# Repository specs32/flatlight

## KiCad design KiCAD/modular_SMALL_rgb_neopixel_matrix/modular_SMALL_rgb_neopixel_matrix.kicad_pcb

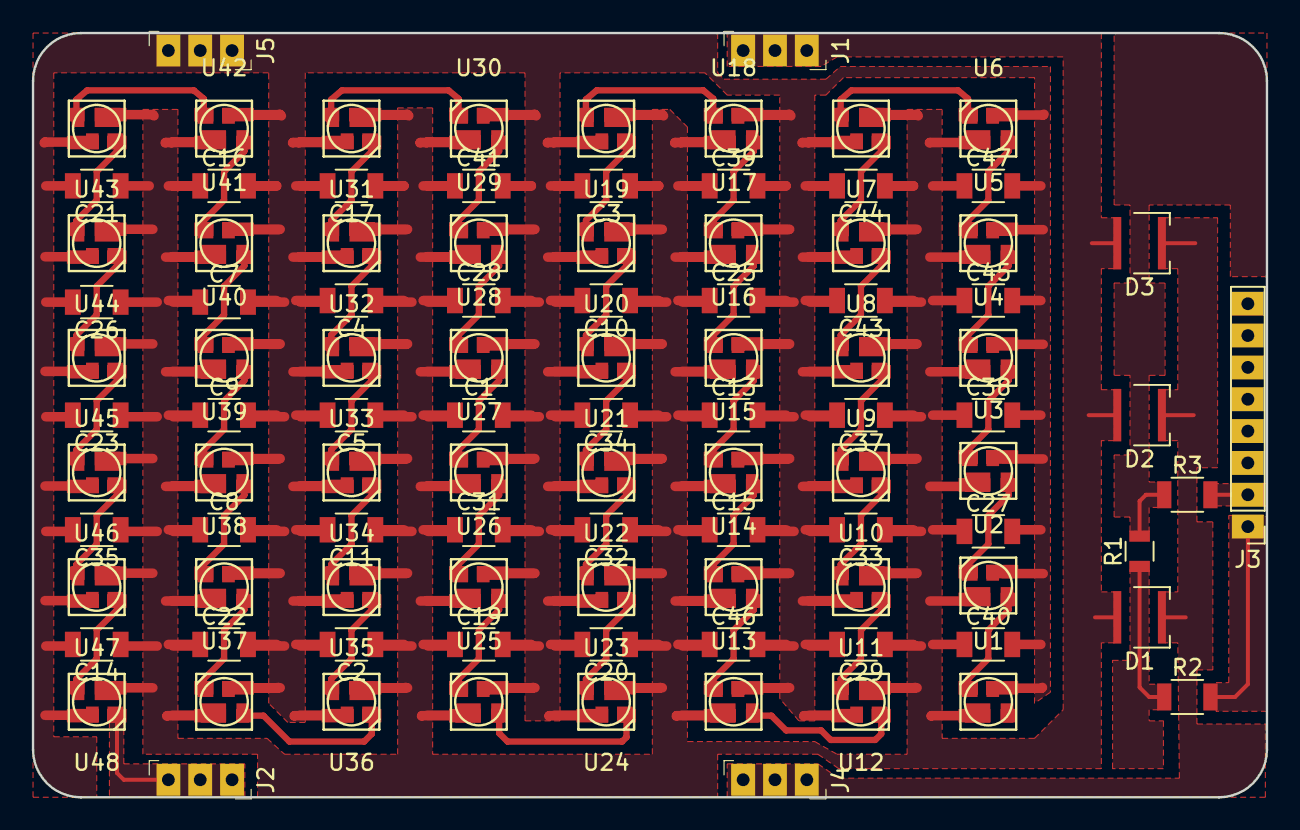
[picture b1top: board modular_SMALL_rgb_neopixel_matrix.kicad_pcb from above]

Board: 2 copper layers, 77.5 x 48.0 mm, 99 parts (0 on the bottom side), 55 nets.

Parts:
C1, C2, C3, C4, C5, C7, C8, C9, C10, C11, C13, C14, C15, C16, C17, C19, C20, C21, C22, C23, C25, C26, C27, C28, C29, C31, C32, C33, C34, C35, C37, C38, C39, C40, C41, C43, C44, C45, C46, C47: 100nF; C_1206
D1, D2, D3: CREE_XP; LED_Cree-XP_x
J1, J2, J4, J5: CONN_01X03; 3pin_through_conn
J3: CONN_01X08; 1x08_Pitch2.00mm_Bigpad
R1: 15KΩ_NTC; R_0805
R2, R3: 0Ω_Bridge; R_1206
U1, U2, U3, U4, U5, U6, U7, U8, U9, U10, U11, U12, U13, U14, U15, U16, U17, U18, U19, U20, U21, U22, U23, U24, U25, U26, U27, U28, U29, U30, U31, U32, U33, U34, U35, U36, U37, U38, U39, U40, U41, U42, U43, U44, U45, U46, U47, U48: RGB_ws2812_3535; SK6812_MINI_right

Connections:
GND: C1.2, C2.2, C3.2, C4.2, C5.2, C7.2, C8.2, C9.2, C10.2, C11.2, C13.2, C14.2, C15.2, C16.2, C17.2, C19.2, C20.2, C21.2, C22.2, C23.2, C25.2, C26.2, C27.2, C28.2, C29.2, C31.2, C32.2, C33.2, C34.2, C35.2, C37.2, C38.2, C39.2, C40.2, C41.2, C43.2, C44.2, C45.2, C46.2, C47.2, J5.1, J5.2, J5.3, U1.2, U2.2, U3.2, U4.2, U5.2, U6.2, U7.2, U8.2, U9.2, U10.2, U11.2, U12.2, U13.2, U14.2, U15.2, U16.2, U17.2, U18.2, U19.2, U20.2, U21.2, U22.2, U23.2, U24.2, U25.2, U26.2, U27.2, U28.2, U29.2, U30.2, U31.2, U32.2, U33.2, U34.2, U35.2, U36.2, U37.2, U38.2, U39.2, U40.2, U41.2, U42.2, U43.2, U44.2, U45.2, U46.2, U47.2, U48.2
unnamed: J3.1, R2.2
unnamed: J3.2, R3.2
unnamed: R1.1, R2.1
unnamed: R1.2, R3.1
unnamed: U1.3, U2.1
unnamed: U2.3, U3.1
unnamed: U3.3, U4.1
unnamed: U4.3, U5.1
unnamed: U5.3, U6.1
unnamed: U6.3, U7.1
unnamed: U7.3, U8.1
unnamed: U8.3, U9.1
unnamed: U9.3, U10.1
unnamed: U10.3, U11.1
unnamed: U11.3, U12.1
unnamed: U12.3, U13.1
unnamed: U13.3, U14.1
unnamed: U14.3, U15.1
unnamed: U15.3, U16.1
unnamed: U16.3, U17.1
unnamed: U17.3, U18.1
unnamed: U18.3, U19.1
unnamed: U19.3, U20.1
unnamed: U20.3, U21.1
unnamed: U21.3, U22.1
unnamed: U22.3, U23.1
unnamed: U23.3, U24.1
unnamed: U24.3, U25.1
unnamed: U25.3, U26.1
unnamed: U26.3, U27.1
unnamed: U27.3, U28.1
unnamed: U28.3, U29.1
unnamed: U29.3, U30.1
unnamed: U30.3, U31.1
unnamed: U31.3, U32.1
unnamed: U32.3, U33.1
unnamed: U33.3, U34.1
unnamed: U34.3, U35.1
unnamed: U35.3, U36.1
unnamed: U36.3, U37.1
unnamed: U37.3, U38.1
unnamed: U38.3, U39.1
unnamed: U39.3, U40.1
unnamed: U40.3, U41.1
unnamed: U41.3, U42.1
unnamed: U42.3, U43.1
unnamed: U43.3, U44.1
unnamed: U44.3, U45.1
unnamed: U45.3, U46.1
unnamed: U46.3, U47.1
unnamed: U47.3, U48.1
OCA_1: J2.1, J2.2, J2.3, U48.3
PWM_1: D1.1, D2.1, D3.1, J4.1, J4.2, J4.3
VCC: C1.1, C2.1, C3.1, C4.1, C5.1, C7.1, C8.1, C9.1, C10.1, C11.1, C13.1, C14.1, C15.1, C16.1, C17.1, C19.1, C20.1, C21.1, C22.1, C23.1, C25.1, C26.1, C27.1, C28.1, C29.1, C31.1, C32.1, C33.1, C34.1, C35.1, C37.1, C38.1, C39.1, C40.1, C41.1, C43.1, C44.1, C45.1, C46.1, C47.1, D1.2, D2.2, D3.2, J1.1, J1.2, J1.3, U1.4, U2.4, U3.4, U4.4, U5.4, U6.4, U7.4, U8.4, U9.4, U10.4, U11.4, U12.4, U13.4, U14.4, U15.4, U16.4, U17.4, U18.4, U19.4, U20.4, U21.4, U22.4, U23.4, U24.4, U25.4, U26.4, U27.4, U28.4, U29.4, U30.4, U31.4, U32.4, U33.4, U34.4, U35.4, U36.4, U37.4, U38.4, U39.4, U40.4, U41.4, U42.4, U43.4, U44.4, U45.4, U46.4, U47.4, U48.4

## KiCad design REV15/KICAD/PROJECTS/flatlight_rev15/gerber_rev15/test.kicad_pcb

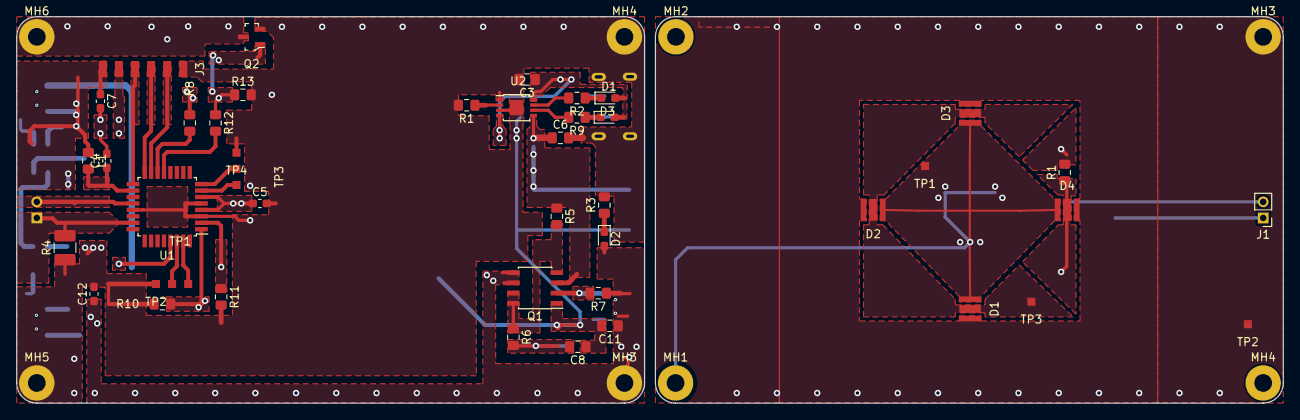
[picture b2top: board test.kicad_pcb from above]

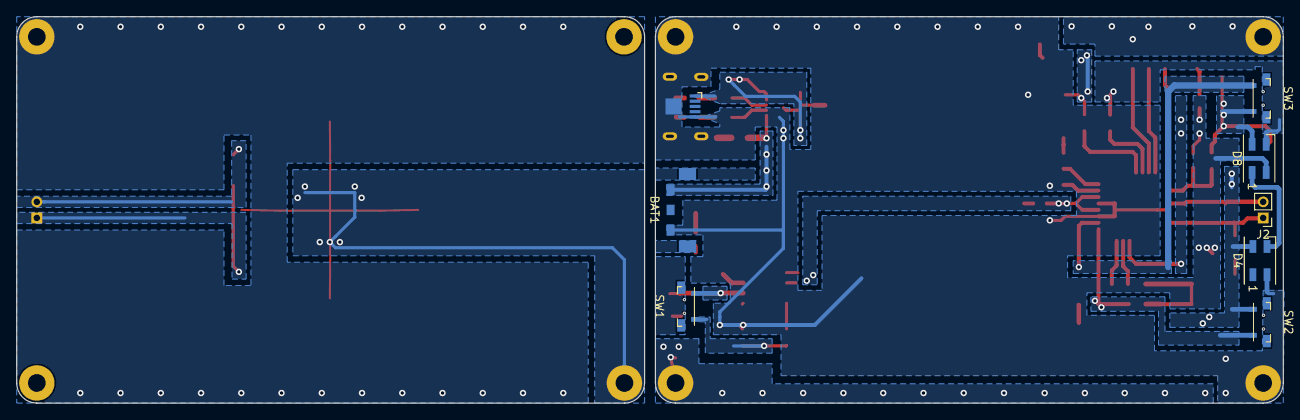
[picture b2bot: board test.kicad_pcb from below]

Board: 2 copper layers, 157.3 x 48.0 mm, 59 parts (8 on the bottom side), 35 nets.

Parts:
BAT1: LIPO_W_NTC; CONN_AVX_RT_ANGLE_3pin_2.5mm_pitch
C3, C6, C11: 10µF; C_0805_2012Metric_Pad1.15x1.40mm_HandSolder
C4, C5, C7, C12: 100nF; C_0603_1608Metric_Pad1.05x0.95mm_HandSolder
C8: 1µF; C_0805_2012Metric_Pad1.15x1.40mm_HandSolder
D1: LED_RED; LED_0603_1608Metric_Pad1.05x0.95mm_HandSolder
D1#2, D2#2, D3#2, D4#2: LED; LED_osram_oslon_ssl_powerled
D2: LED_PINK; LED_0603_1608Metric_Pad1.05x0.95mm_HandSolder
D3: LED_GREEN; LED_0603_1608Metric_Pad1.05x0.95mm_HandSolder
D4, D8: SK6812MINI; LED_SK6812MINI_PLCC4_3.5x3.5mm_P1.75mm
J1: USB_B_Micro; Conn_USBmicro-B_ebay-side_TH_GROUND
J1#2: Conn_01x02_Male; PinHeader_1x02_P2.00mm_Vertical
J2: TEMP_SENSOR; PinHeader_1x02_P2.00mm_Vertical
J3: ISP_CONN; Conn_01x06_SMD_2mm
L1: 10µH; L_0805_2012Metric_Pad1.15x1.40mm_HandSolder
MH1, MH3: VCC; MountingHole_2.2mm_M2_Pad
MH2, MH4, MH4#2, MH5: GND; MountingHole_2.2mm_M2_Pad
MH3#2: SOURCE; MountingHole_2.2mm_M2_Pad
MH6: OC1A; MountingHole_2.2mm_M2_Pad
Q1: IRF7343PBF; SOIC-8_3.9x4.9mm_P1.27mm
Q2: IRLML6344TRPBF; SOT-23-3
R1: 1.2kΩ; R_0805_2012Metric_Pad1.15x1.40mm_HandSolder
R1#2: R; R_0805_2012Metric_Pad1.15x1.40mm_HandSolder
R2, R3, R8, R9, R12: 1kΩ; R_0805_2012Metric_Pad1.15x1.40mm_HandSolder
R4: 15kΩ; R_1210_3225Metric_Pad1.42x2.65mm_HandSolder
R5, R7, R10, R11: 10kΩ; R_0805_2012Metric_Pad1.15x1.40mm_HandSolder
R6: 100kΩ; R_0805_2012Metric_Pad1.15x1.40mm_HandSolder
R13: 1MΩ; R_0805_2012Metric_Pad1.15x1.40mm_HandSolder
SW1: nano_sw; white_nano_smd_switch
SW2, SW3: SW_DIP_x01; white_nano_smd_switch
TP1: COM; 2_pad_smd_bat_conn
TP1#2: VCC; 1_pad_smd
TP2, TP4: TestPoint; 1_pad_smd
TP2#2: SOURCE; 1_pad_smd
TP3: OSC; 2_pad_smd_bat_conn
TP3#2: THERM; 1_pad_smd
U1: ATmega88-20AU; TQFP-32_7x7mm_P0.8mm
U2: DIO5158; MSOP-8-1EP_3x3mm_P0.65mm_EP1.68x1.88mm

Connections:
+BATT: BAT1.1, C6.1, Q1.3, R5.1, U2.5
ADC0: J2.1, R4.2, U1.23
AREF: J2.2, U1.20
AVCC: C4.1, L1.2, U1.18
GND: BAT1.3, C3.2, C4.2, C5.2, C6.2, C7.2, C8.1, C11.2, C12.2, D1#2.1, D2#2.1, D3#2.1, D4.2, D4#2.1, D8.2, J1.5, J1.6, J3.1, MH3#2.1, MH4.1, MH5.1, Q1.1, Q2.2, R1.2, R3.2, R4.1, R10.2, R11.2, R13.2, TP2.1, TP2#2.1, TP4.1, U1.3, U1.5, U1.21, U2.1, U2.3, U2.9
MISO: J3.3, U1.16
MOSI: J3.2, U1.15
unnamed: C8.2, R6.2, SW1.1
unnamed: D1.1, R2.1
unnamed: D2.1, R3.1
unnamed: D3.1, R9.1
unnamed: D4.3, D8.1
unnamed: D8.3, R8.2
unnamed: D4#2.3, J1#2.1, R1#2.1
unnamed: J1.2, J1#2.2, R1#2.2
unnamed: MH6.1, Q2.3
unnamed: Q1.2, R7.2, SW1.2
unnamed: Q1.4, Q1.7, Q1.8, R5.2, R6.1
unnamed: Q2.1, R12.1, R13.1
unnamed: R1.1, U2.2
unnamed: R2.2, U2.7
unnamed: R9.2, U2.6
OC1A: R12.2, U1.13
OC1B: R8.1, U1.14
OSC_N: TP3.1, U1.7
OSC_P: TP3.2, U1.8
PD3: R10.1, SW2.2, U1.1
PD4: R11.1, SW3.1, U1.2
RESET: J3.5, U1.29
RX: TP1.2, U1.30
SCK: J3.4, U1.17
TX: TP1.1, U1.31
VBUS: C3.1, D1.2, D3.2, J1.1, U2.4, U2.8
VCC: C5.1, C7.1, C11.1, C12.1, D1#2.2, D2.2, D2#2.2, D3#2.2, D4.4, D4#2.2, D8.4, J3.6, L1.1, MH1.1, MH3.1, Q1.5, Q1.6, R7.1, SW2.1, SW3.2, TP1#2.1, U1.4, U1.6
therm: D1#2.3, D2#2.3, D3#2.3, TP3#2.1

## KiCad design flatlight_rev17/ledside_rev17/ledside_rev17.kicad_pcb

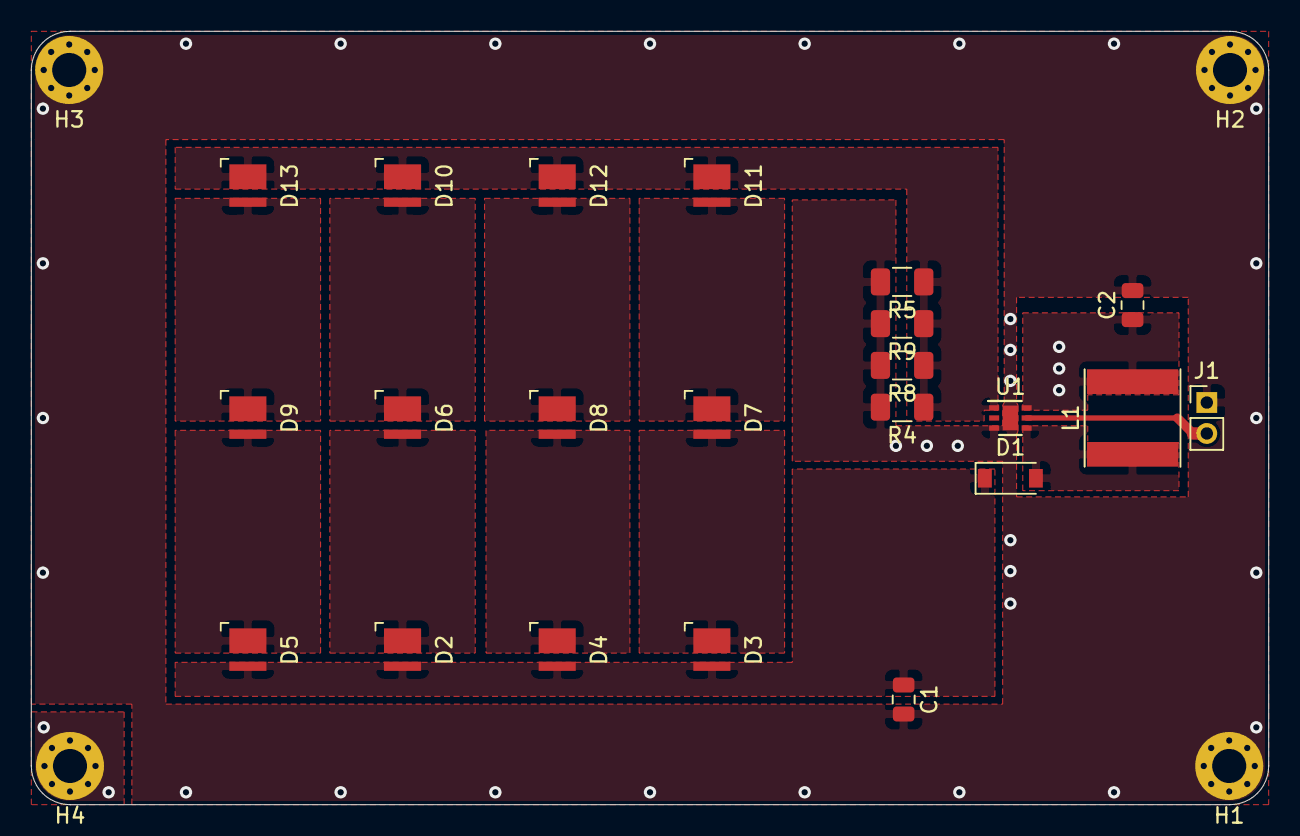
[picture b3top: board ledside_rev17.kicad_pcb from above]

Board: 2 copper layers, 80.0 x 50.0 mm, 30 parts (1 on the bottom side), 14 nets.

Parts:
C1, C2: C; C_0805_2012Metric
D1: D; D_SOD-123
D2, D3, D4, D5, D6, D7, D8, D9, D10, D11, D12, D13: LED; LED_Cree-J-Series
H1, H2, H3, H4: MountingHole_Pad; MountingHole_2.2mm_M2_Pad_Via
J1: Conn_01x02_Male; PinHeader_1x02_P2.00mm_Vertical
L1: INDUCTOR; L_Taiyo-Yuden_NR-60xx
R4, R5, R8, R9: R; R_1206_3216Metric
U1: dio5661; DFN-6-1EP_2x2mm_P0.65mm_EP1x1.6mm
logo1: logo_LIGHTWARN; logo_light_warn
logo2: logo_contact; logo_QR-tag_rev16
logo3: logo-cc-by-sa; cc-by-sa
logo4: logo_Ledside17; logo_ledsiderev17

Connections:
EN: J1.2, U1.5
GND: C1.2, C2.2, H1.1, H2.1, H3.1, J1.1, R4.2, R5.2, R8.2, R9.2, U1.3, U1.7
LX: D1.2, L1.1, U1.4
unnamed: C1.1, D1.1, D2.2, D3.2, D4.2, D5.2
unnamed: D2.1, D6.2
unnamed: D3.1, D7.2
unnamed: D4.1, D8.2
unnamed: D5.1, D9.2
unnamed: D10.1, D11.1, D12.1, D13.1, R4.1, R5.1, R8.1, R9.1, U1.1
unnamed: D6.1, D10.2
unnamed: D7.1, D11.2
unnamed: D8.1, D12.2
unnamed: D9.1, D13.2
VCC: C2.1, H4.1, L1.2, U1.6
